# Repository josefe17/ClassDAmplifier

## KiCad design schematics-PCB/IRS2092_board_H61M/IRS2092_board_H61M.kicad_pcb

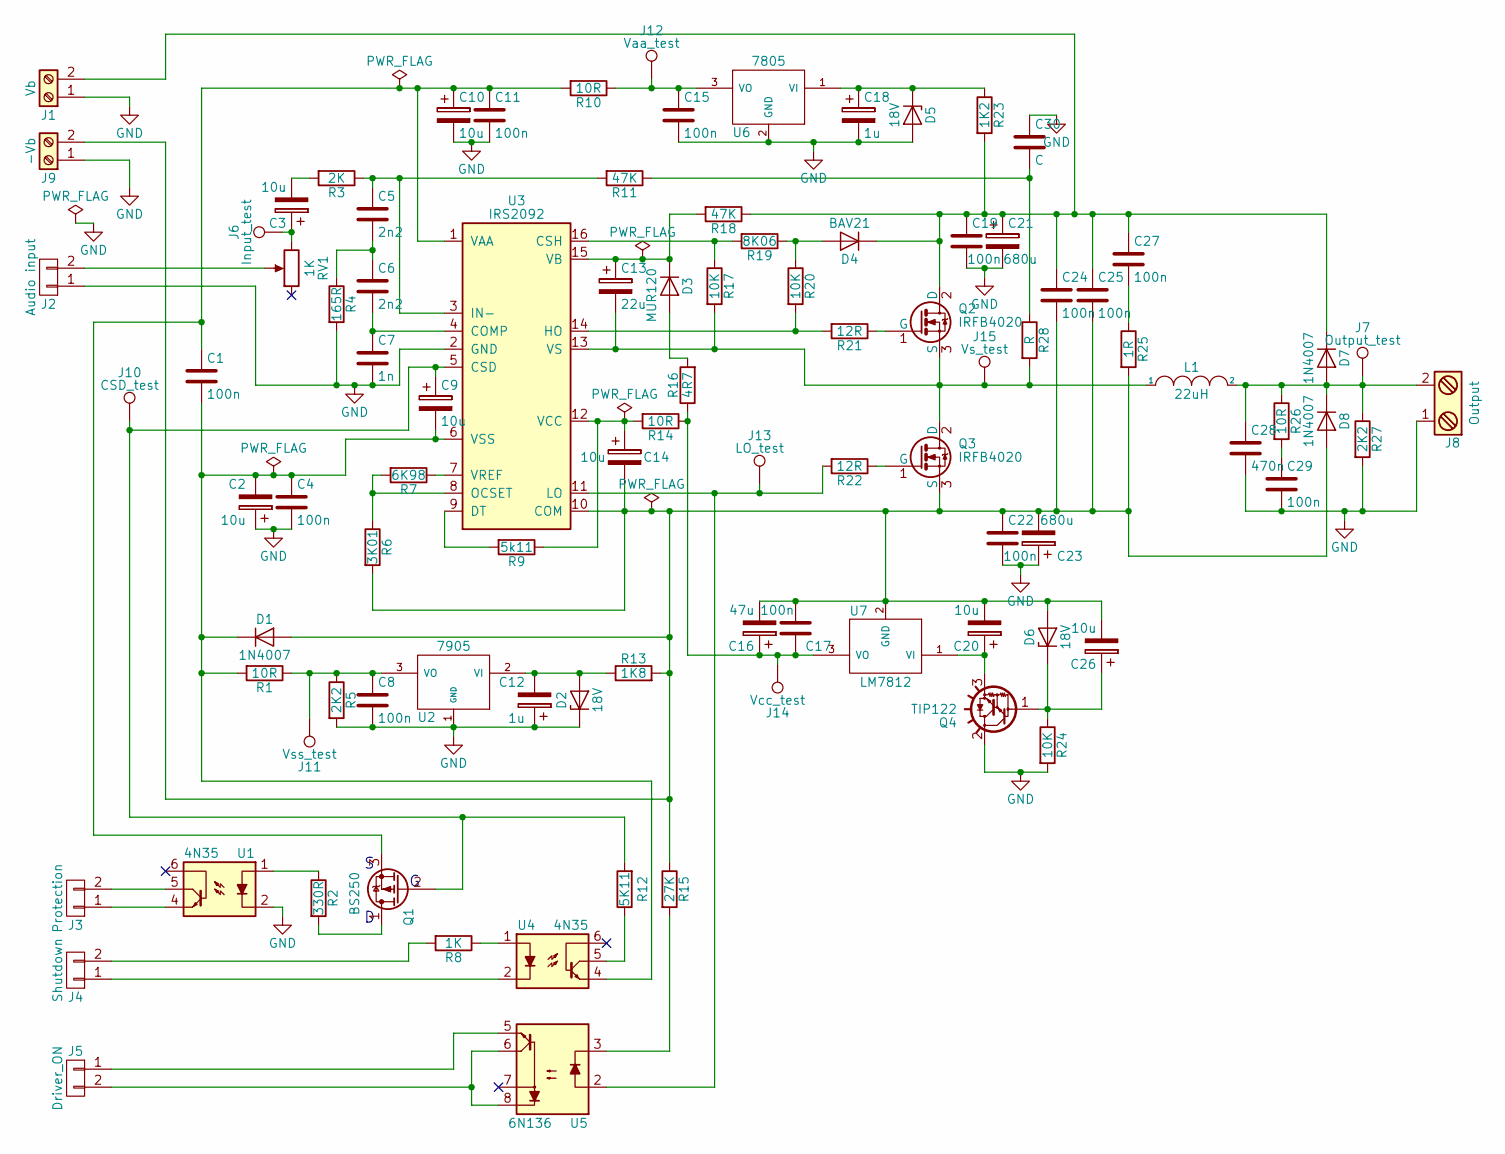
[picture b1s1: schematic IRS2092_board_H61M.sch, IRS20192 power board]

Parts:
C1, C4, C8, C11, C15, C17: 100n; C_Rect_L7.0mm_W2.5mm_P5.00mm
C2, C3, C9, C10, C14, C20, C26: 10u; CP_Radial_D8.0mm_P2.50mm
C5, C6: 2n2; C_Rect_L7.0mm_W2.5mm_P5.00mm
C7: 1n; C_Rect_L7.0mm_W2.5mm_P5.00mm
C12, C18: 1u; CP_Radial_D8.0mm_P2.50mm
C13: 22u; CP_Radial_D6.3mm_P2.50mm
C16: 47u; CP_Radial_D5.0mm_P2.00mm
C19, C22, C24, C25, C27, C29: 100n; C_Rect_L11.5mm_W4.0mm_P10.00mm_MKT
C21, C23: 680u; CP_Radial_D30.0mm_P10.00mm_SnapIn
C28: 470n; C_Rect_L16.5mm_W8.9mm_P15.00mm_MKT
C30: C; C_Rect_L7.0mm_W2.5mm_P5.00mm
D1, D7, D8: 1N4007; D_DO-41_SOD81_P10.16mm_Horizontal
D2, D5, D6: 18V; D_DO-41_SOD81_P10.16mm_Horizontal
D3: MUR120; D_DO-41_SOD81_P10.16mm_Horizontal
D4: BAV21; D_DO-35_SOD27_P10.16mm_Horizontal
J1: Vb; TerminalBlock_bornier-2_P5.08mm
J2: Audio input; Molex_KK-6410-02_02x2.54mm_Straight
J3: Protection; Molex_KK-6410-02_02x2.54mm_Straight
J4: Shutdown; Molex_KK-6410-02_02x2.54mm_Straight
J5: Driver_ON; Molex_KK-6410-02_02x2.54mm_Straight
J6: Input_test; PINTST
J7: Output_test; PINTST
J8: Output; TerminalBlock_bornier-2_P5.08mm
J9: -Vb; TerminalBlock_bornier-2_P5.08mm
J10: CSD_test; PINTST
J11: Vss_test; PINTST
J12: Vaa_test; PINTST
J13: LO_test; PINTST
J14: Vcc_test; PINTST
J15: Vs_test; PINTST
L1: 22uH; L_Toroid_Vertical_L41.9mm_W19.1mm_P15.80mm_Vishay_TJ7
Q1: BS250; TO-92_Inline_Narrow_Oval
Q2, Q3: IRFB4020; TO-220-3_Vertical
Q4: TIP122; TO-220-3_Vertical
R1, R10, R14: 10R; R_Axial_DIN0207_L6.3mm_D2.5mm_P10.16mm_Horizontal
R2: 330R; R_Axial_DIN0207_L6.3mm_D2.5mm_P10.16mm_Horizontal
R3: 2K; R_Axial_DIN0207_L6.3mm_D2.5mm_P10.16mm_Horizontal
R4: 165R; R_Axial_DIN0207_L6.3mm_D2.5mm_P10.16mm_Horizontal
R5: 2K2; R_Axial_DIN0207_L6.3mm_D2.5mm_P10.16mm_Horizontal
R6: 3K01; R_Axial_DIN0207_L6.3mm_D2.5mm_P10.16mm_Horizontal
R7: 6K98; R_Axial_DIN0207_L6.3mm_D2.5mm_P10.16mm_Horizontal
R8: 1K; R_Axial_DIN0207_L6.3mm_D2.5mm_P10.16mm_Horizontal
R9: 5k11; R_Axial_DIN0207_L6.3mm_D2.5mm_P10.16mm_Horizontal
R11, R18: 47K; R_Axial_DIN0207_L6.3mm_D2.5mm_P10.16mm_Horizontal
R12: 5K11; R_Axial_DIN0207_L6.3mm_D2.5mm_P10.16mm_Horizontal
R13: 1K8; R_Axial_DIN0516_L15.5mm_D5.0mm_P20.32mm_Horizontal
R15: 27K; R_Axial_DIN0207_L6.3mm_D2.5mm_P10.16mm_Horizontal
R16: 4R7; R_Axial_DIN0207_L6.3mm_D2.5mm_P10.16mm_Horizontal
R17, R20, R24: 10K; R_Axial_DIN0207_L6.3mm_D2.5mm_P10.16mm_Horizontal
R19: 8K06; R_Axial_DIN0207_L6.3mm_D2.5mm_P10.16mm_Horizontal
R21, R22: 12R; R_Axial_DIN0207_L6.3mm_D2.5mm_P10.16mm_Horizontal
R23: 1K2; R_Axial_DIN0516_L15.5mm_D5.0mm_P20.32mm_Horizontal
R25: 1R; R_Axial_DIN0516_L15.5mm_D5.0mm_P20.32mm_Horizontal
R26: 10R; R_Axial_DIN0516_L15.5mm_D5.0mm_P20.32mm_Horizontal
R27: 2K2; R_Axial_DIN0516_L15.5mm_D5.0mm_P20.32mm_Horizontal
R28: R; R_Axial_DIN0207_L6.3mm_D2.5mm_P10.16mm_Horizontal
RV1: 1K; Potentiometer_Trimmer_Vishay_T73XX_Vertical
U1, U4: 4N35; DIP-6_W7.62mm
U2: 7905; TO-220-3_Vertical
U3: IRS2092; SOIC-16_3.9x9.9mm_Pitch1.27mm
U5: 6N136; DIP-8_W7.62mm
U6: 7805; TO-220-3_Vertical
U7: LM7812; TO-220-3_Vertical

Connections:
GND: C2.1, C4.2, C7.2, C8.2, C10.2, C11.2, C12.1, C15.2, C18.2, C19.2, C21.2, C22.2, C23.1, C28.2, C29.2, C30.1, D2.1 (K), D5.2 (A), J1.1, J2.1, J8.1, J9.1, Q4.2 (C), R4.2, R5.2, R24.2, R27.2, U1.2, U2.1 (GND), U3.2 (GND), U6.2 (GND)
unnamed: C1.1, C10.1, C11.1, Q1.3 (S), R10.2, U3.1 (VAA)
unnamed: C1.2, C2.2, C4.1, C9.2, D1.1 (K), R1.2, U3.6 (VSS), U4.4
unnamed: C3.1, J6.1, RV1.3
unnamed: C3.2, R3.2
unnamed: C5.1, R3.1, R11.2, U3.3 (IN-)
unnamed: C5.2, C6.1, R4.1
unnamed: C6.2, C7.1, U3.4 (COMP)
unnamed: C8.1, J11.1, R1.1, R5.1, U2.3 (VO)
unnamed: C9.1, J10.1, Q1.2 (G), R12.2, U3.5 (CSD)
unnamed: C12.2, D2.2 (A), R13.1, U2.2 (VI)
unnamed: C13.1, D3.1 (K), R18.2, U3.15 (VB)
unnamed: C13.2, J15.1, L1.1, Q2.3 (S), Q3.2 (D), R17.2, R28.2, U3.13 (VS)
unnamed: C14.1, R9.1, R14.2, U3.12 (VCC)
unnamed: C14.2, C16.2, C17.1, C20.2, C22.1, C23.2, C24.2, C25.2, C26.2, D1.2 (A), D6.2 (A), D8.2 (A), J9.2, Q3.3 (S), R6.2, R13.2, R15.1, R25.2, U3.10 (COM), U7.2 (GND)
unnamed: C15.1, J12.1, R10.1, U6.3 (VO)
unnamed: C16.1, C17.2, J14.1, R14.1, R16.1, U7.3 (VO)
unnamed: C18.1, D5.1 (K), R23.1, U6.1 (VI)
unnamed: C19.1, C21.1, C24.1, C25.1, C27.1, D4.1 (K), D7.1 (K), J1.2, Q2.2 (D), R18.1, R23.2
unnamed: C20.1, Q4.3 (E), U7.1 (VI)
unnamed: C26.1, D6.1 (K), Q4.1 (B), R24.1
unnamed: C27.2, R25.1
unnamed: C28.1, D7.2 (A), D8.1 (K), J7.1, J8.2, L1.2, R26.1, R27.1
unnamed: C29.1, R26.2
unnamed: C30.2, R11.1, R28.1
unnamed: D3.2 (A), R16.2
unnamed: D4.2 (A), R19.1, R20.1
unnamed: J2.2, RV1.2
unnamed: J3.1, U1.4
unnamed: J3.2, U1.5
unnamed: J4.1, U4.2
unnamed: J4.2, R8.2
unnamed: J5.1, U5.5
unnamed: J5.2, U5.6, U5.8
unnamed: J13.1, R22.2, U3.11 (LO), U5.2
unnamed: Q1.1 (D), R2.2
unnamed: Q2.1 (G), R21.1
unnamed: Q3.1 (G), R22.1
unnamed: R2.1, U1.1
unnamed: R6.1, R7.2, U3.8 (OCSET)
unnamed: R7.1, U3.7 (VREF)
unnamed: R8.1, U4.1
unnamed: R9.2, U3.9 (DT)
unnamed: R12.1, U4.5
unnamed: R15.2, U5.3
unnamed: R17.1, R19.2, U3.16 (CSH)
unnamed: R20.2, R21.2, U3.14 (HO)

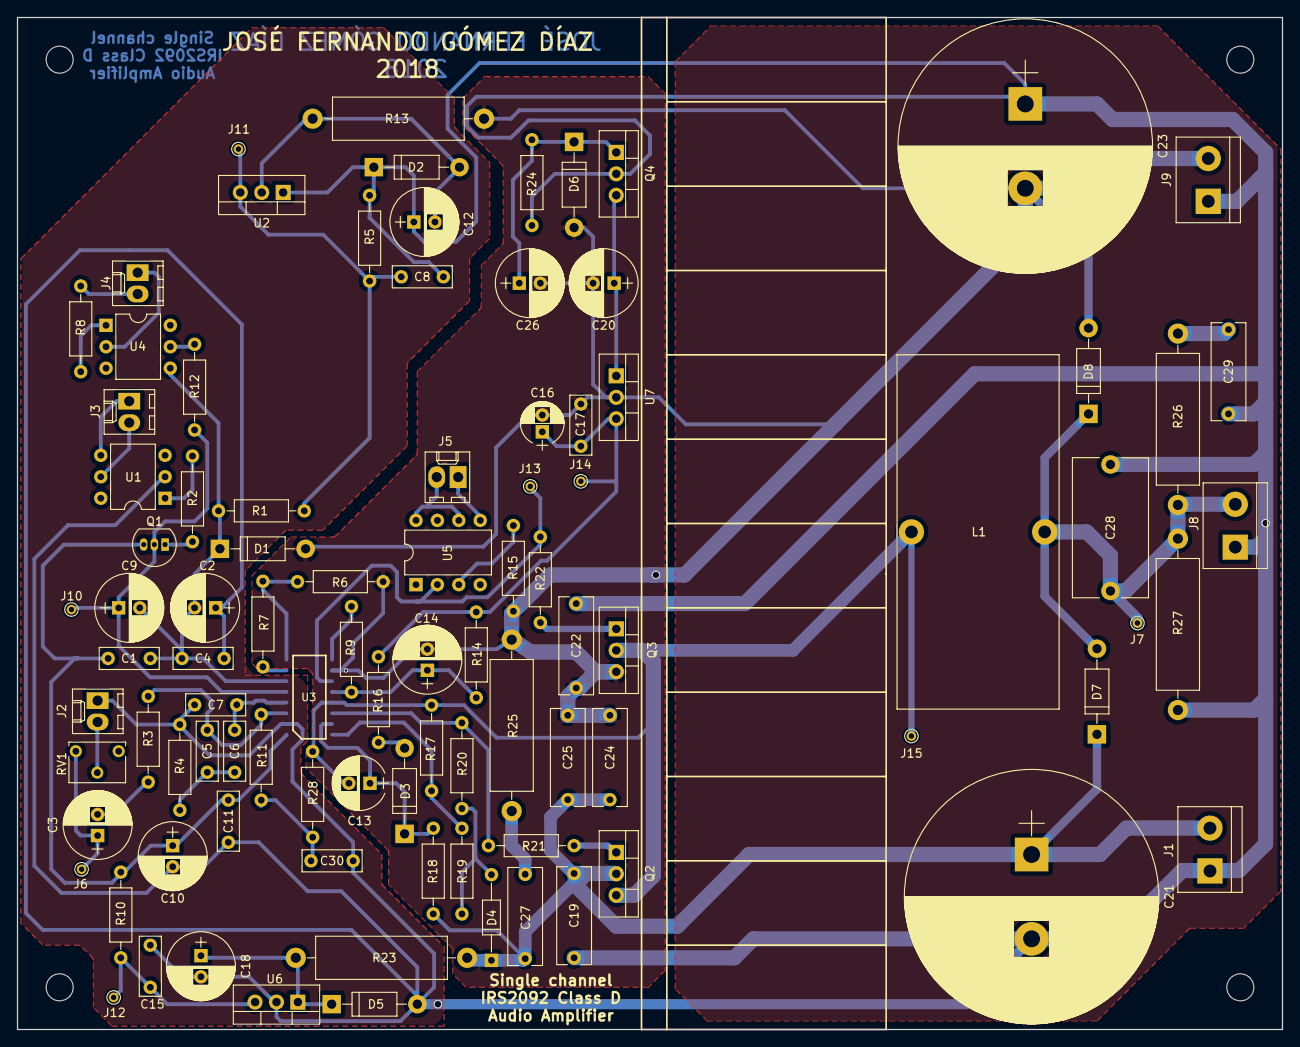
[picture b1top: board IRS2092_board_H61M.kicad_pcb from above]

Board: 2 copper layers, 150.0 x 120.0 mm, 96 parts (1 on the bottom side), 47 nets.

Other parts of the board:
 : MountingHole_3.2mm_M3
 #2: MountingHole_3.2mm_M3

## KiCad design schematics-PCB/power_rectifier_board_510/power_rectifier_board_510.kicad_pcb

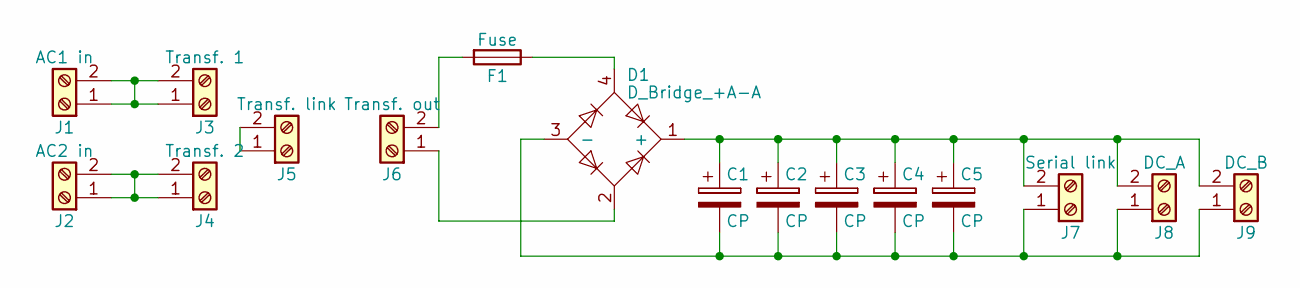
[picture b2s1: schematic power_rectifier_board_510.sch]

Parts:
C1, C2, C3: CP; CP_Radial_D30.0mm_P10.00mm_SnapIn
C4: CP; CP_Radial_D22.0mm_P10.00mm_SnapIn
C5: CP; CP_Radial_D18.0mm_P7.50mm
D1: D_Bridge_+A-A; bridge_kbpc_3506
F1: Fuse; Fuseholder5x20_horiz_open_universal_RSP
J1: AC1 in; TerminalBlock_bornier-2_P5.08mm
J2: AC2 in; TerminalBlock_bornier-2_P5.08mm
J3: Transf. 1; TerminalBlock_bornier-2_P5.08mm
J4: Transf. 2; TerminalBlock_bornier-2_P5.08mm
J5: Transf. link; TerminalBlock_bornier-2_P5.08mm
J6: Transf. out; TerminalBlock_bornier-2_P5.08mm
J7: Serial link; TerminalBlock_bornier-2_P5.08mm
J8: DC_A; TerminalBlock_bornier-2_P5.08mm
J9: DC_B; TerminalBlock_bornier-2_P5.08mm

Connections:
unnamed: C1.1, C2.1, C3.1, C4.1, C5.1, D1.1 (+), J7.2, J8.2, J9.2
unnamed: C1.2, C2.2, C3.2, C4.2, C5.2, D1.3 (-), J7.1, J8.1, J9.1
unnamed: D1.2, J6.1
unnamed: D1.4, F1.1
unnamed: F1.2, J6.2
unnamed: J1.1, J1.2, J3.1, J3.2
unnamed: J2.1, J2.2, J4.1, J4.2
unnamed: J5.1, J5.2

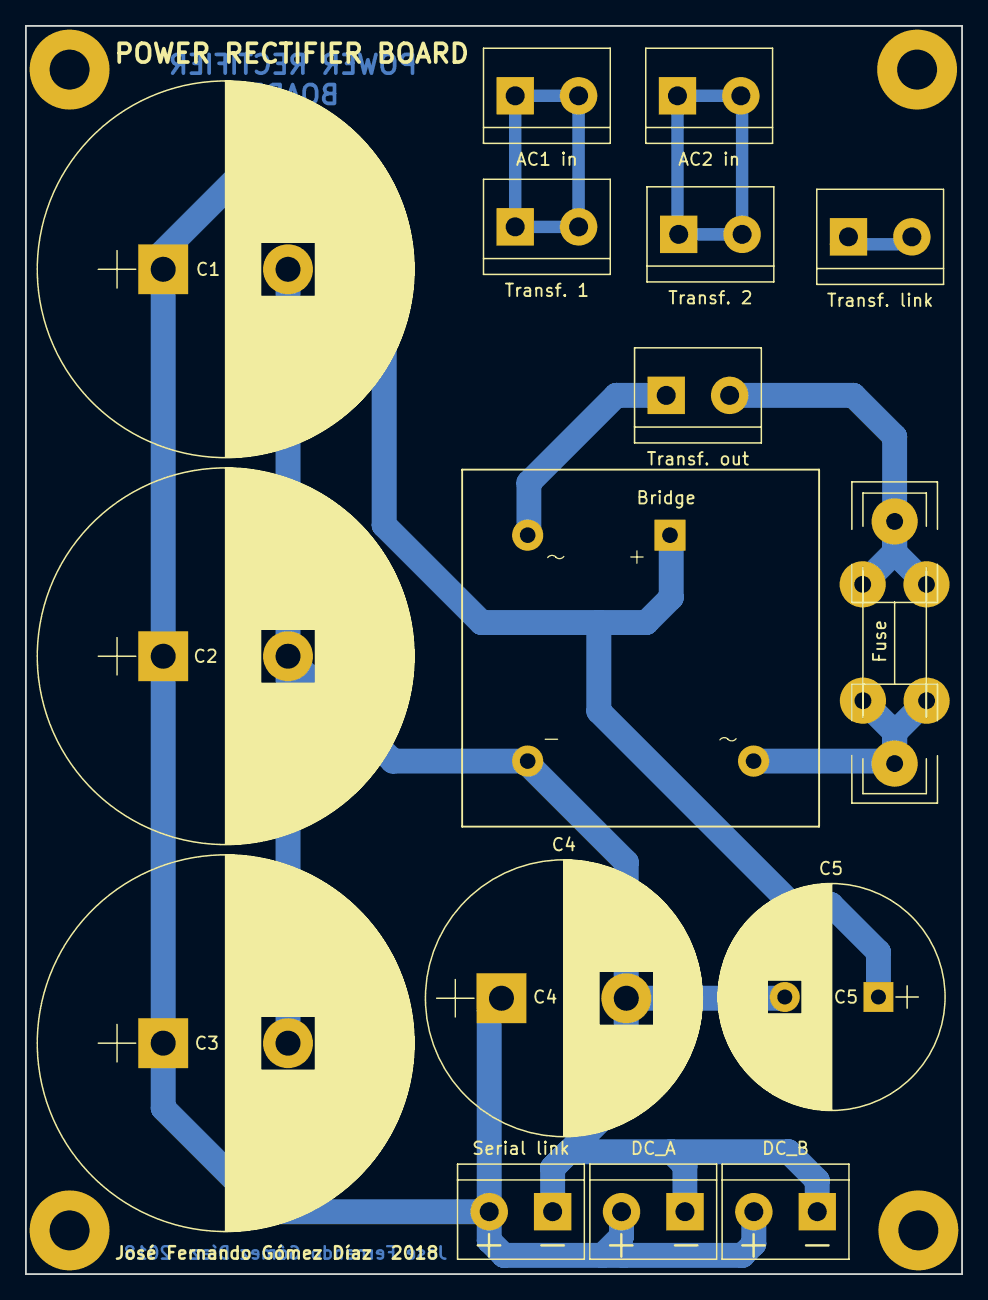
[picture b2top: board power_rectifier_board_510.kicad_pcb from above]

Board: 2 copper layers, 75.0 x 100.0 mm, 17 parts (0 on the bottom side), 8 nets.

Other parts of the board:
 Ref**: MountingHole_3.2mm_M3_Pad

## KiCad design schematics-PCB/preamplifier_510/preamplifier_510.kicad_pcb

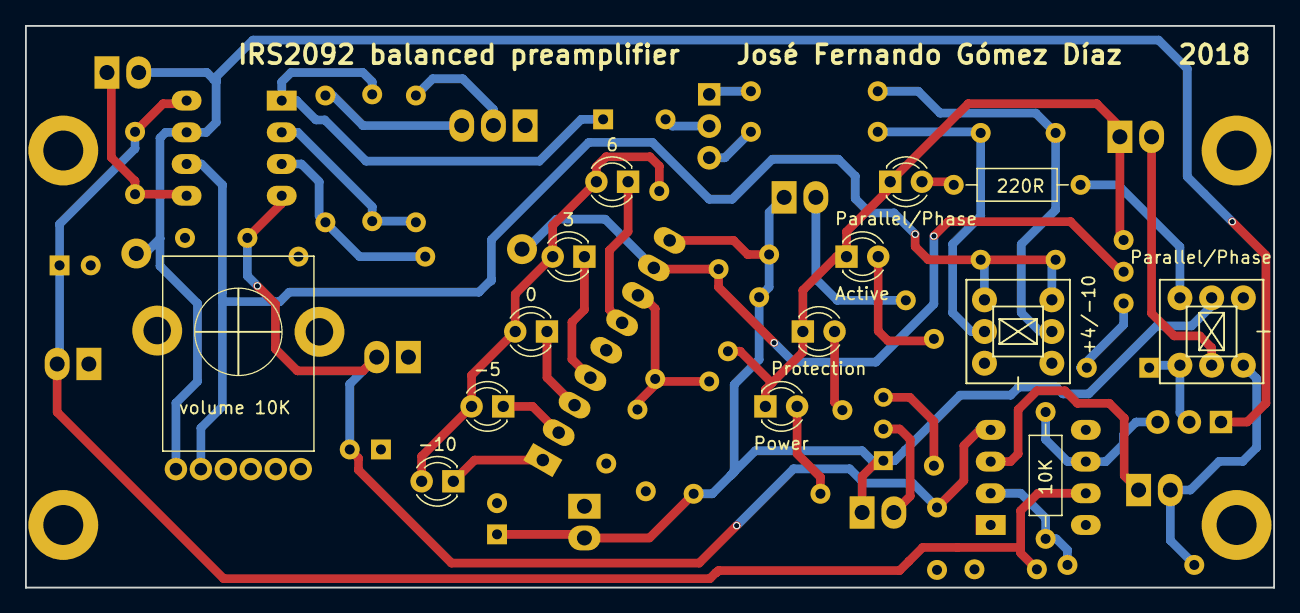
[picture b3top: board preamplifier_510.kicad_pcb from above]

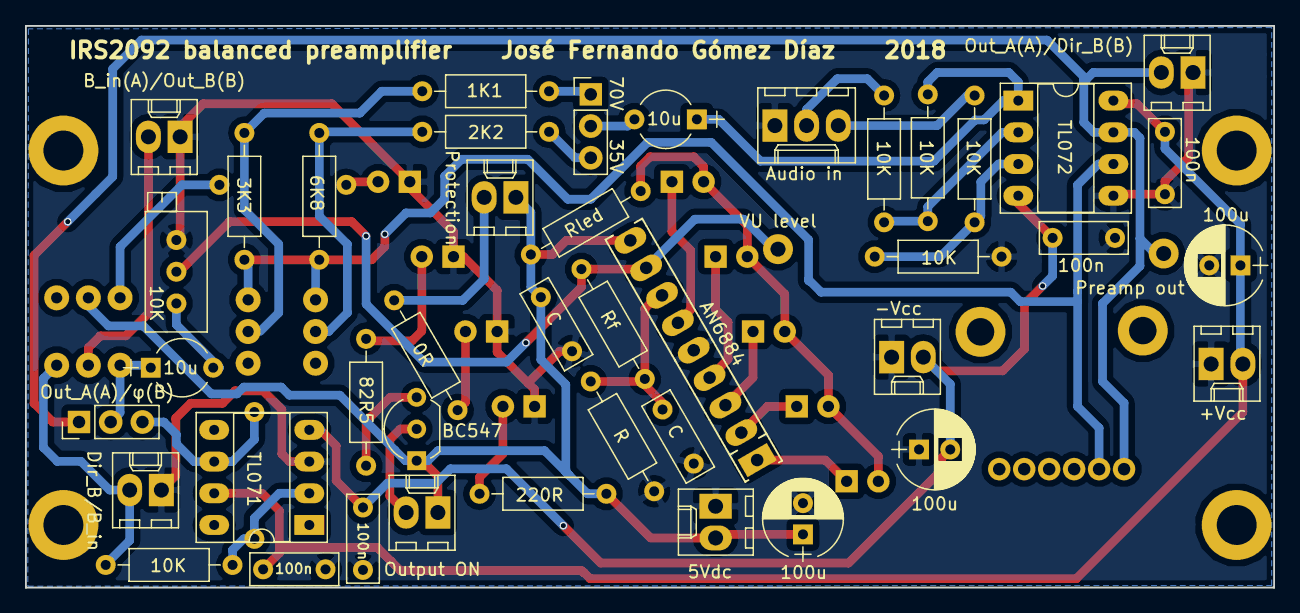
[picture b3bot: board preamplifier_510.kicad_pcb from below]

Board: 2 copper layers, 100.0 x 45.0 mm, 58 parts (44 on the bottom side), 38 nets.

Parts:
C1, C8, C9: 100u; CP_Radial_D6.3mm_P2.50mm
C3, C6: 10u; CP_Radial_Tantal_D4.5mm_P5.00mm
C4, C7: C; C_Rect_L7.0mm_W2.5mm_P5.00mm
C10, C11, C12, C13: 100n; C_Rect_L7.0mm_W2.5mm_P5.00mm
D1: Power; LED_D3.0mm
D2: Parallel/Phase; LED_D3.0mm
D3: Active; LED_D3.0mm
D4: Protection; LED_D3.0mm
D5: -10; LED_D3.0mm
D6: -5; LED_D3.0mm
D7: 0; LED_D3.0mm
D8: 3; LED_D3.0mm
D9: 6; LED_D3.0mm
J1: 5Vdc; Molex_KK-6410-02_02x2.54mm_Straight
J2: Audio in; Molex_KK-6410-03_03x2.54mm_Straight
J4: Output ON; Molex_KK-6410-02_02x2.54mm_Straight
J5: Protection; Molex_KK-6410-02_02x2.54mm_Straight
J6: -Vcc; Molex_KK-6410-02_02x2.54mm_Straight
J7: +Vcc; Molex_KK-6410-02_02x2.54mm_Straight
J8: Out_A(A)/Dir_B(B); Molex_KK-6410-02_02x2.54mm_Straight
J9: Dir_B/B_in; Molex_KK-6410-02_02x2.54mm_Straight
J10: B_in(A)/Out_B(B); Molex_KK-6410-02_02x2.54mm_Straight
J11: VU level; PINTST
J12: Preamp out; PINTST
JP1: 70V 35V; Pin_Header_Straight_1x03_Pitch2.54mm
JP2: Out_A(A)/φ(B); Pin_Header_Straight_1x03_Pitch2.54mm
Q1: BC547; TO-92_Inline_Wide
R1, R2: 220R; R_Axial_DIN0207_L6.3mm_D2.5mm_P10.16mm_Horizontal
R3, R4, R6, R7, R15, R16: 10K; R_Axial_DIN0207_L6.3mm_D2.5mm_P10.16mm_Horizontal
R5: 82R5; R_Axial_DIN0207_L6.3mm_D2.5mm_P10.16mm_Horizontal
R8: 0R; R_Axial_DIN0207_L6.3mm_D2.5mm_P10.16mm_Horizontal
R9: 1K1; R_Axial_DIN0207_L6.3mm_D2.5mm_P10.16mm_Horizontal
R10: 2K2; R_Axial_DIN0207_L6.3mm_D2.5mm_P10.16mm_Horizontal
R11: R; R_Axial_DIN0207_L6.3mm_D2.5mm_P10.16mm_Horizontal
R12: 3K3; R_Axial_DIN0207_L6.3mm_D2.5mm_P10.16mm_Horizontal
R13: 6K8; R_Axial_DIN0207_L6.3mm_D2.5mm_P10.16mm_Horizontal
R14: Rled; R_Axial_DIN0207_L6.3mm_D2.5mm_P10.16mm_Horizontal
R17: Rf; R_Axial_DIN0207_L6.3mm_D2.5mm_P10.16mm_Horizontal
RV1: volume 10K; Potentiometer_Alps_RK12L_Horizontal
RV2: 10K; Potentiometer_Trimmer_Bourns_3296X
SW1: Parallel/Phase; DPDT_Pushbutton
SW2: +4/-10; DPDT_Pushbutton
U1: TL072; DIP-8_W7.62mm_Socket_LongPads
U2: AN6884; SIP9_Housing_BigPads
U3: TL071; DIP-8_W7.62mm_Socket_LongPads

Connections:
GND: C1.2, C4.2, C7.2, C8.1, C9.2, C10.1, C11.2, C12.1, C13.2, D1.1, D2.1, D3.1, D4.1, J1.1, J2.1, J6.1, J7.1, J8.1, J9.1, J10.1, R6.2, R11.2, RV2.3, U1.5, U2.5, U3.3
unnamed: C1.1, C4.1, J1.2, J4.1, J5.1, Q1.1, R1.1, R14.2, SW1.2, U2.9
unnamed: C3.1, R7.1, U1.1
unnamed: C3.2, JP1.2
unnamed: C6.1, JP2.2, SW1.6
unnamed: C6.2, RV2.1
unnamed: C7.1, R11.1, R17.2, U2.7
unnamed: C8.2, C10.2, C12.2, J6.2, U1.4, U3.4
unnamed: C9.1, C11.1, C13.1, J7.2, U1.8, U3.7
unnamed: D1.2, R1.2
unnamed: D2.2, R2.2
unnamed: D3.2, R5.2
unnamed: D4.2, R8.2
unnamed: D5.1, U2.1
unnamed: D5.2, D6.2, D7.2, D8.2, D9.2, R14.1
unnamed: D6.1, U2.2
unnamed: D7.1, U2.3
unnamed: D8.1, U2.4
unnamed: D9.1, U2.6
unnamed: J2.2, R3.2
unnamed: J2.3, R4.2
unnamed: J4.2, Q1.2
unnamed: J5.2, R8.1
unnamed: J9.2, R15.2, SW1.4
unnamed: J10.2, SW1.5
unnamed: J11.1, R17.1, RV2.2, U2.8
unnamed: J8.2, J12.1, JP2.1, RV1.3, U1.7
unnamed: JP1.1, R9.2
unnamed: JP1.3, R10.2
unnamed: JP2.3, R16.1, U3.6
unnamed: Q1.3, R5.1
unnamed: R2.1, SW1.3
unnamed: R3.1, R7.2, U1.2
unnamed: R4.1, R6.1, U1.3
unnamed: R10.1, R13.2, SW2.5
unnamed: R12.1, R13.1, RV1.1, SW2.3, SW2.6, U1.6
unnamed: R9.1, R12.2, SW2.2
unnamed: R15.1, R16.2, U3.2

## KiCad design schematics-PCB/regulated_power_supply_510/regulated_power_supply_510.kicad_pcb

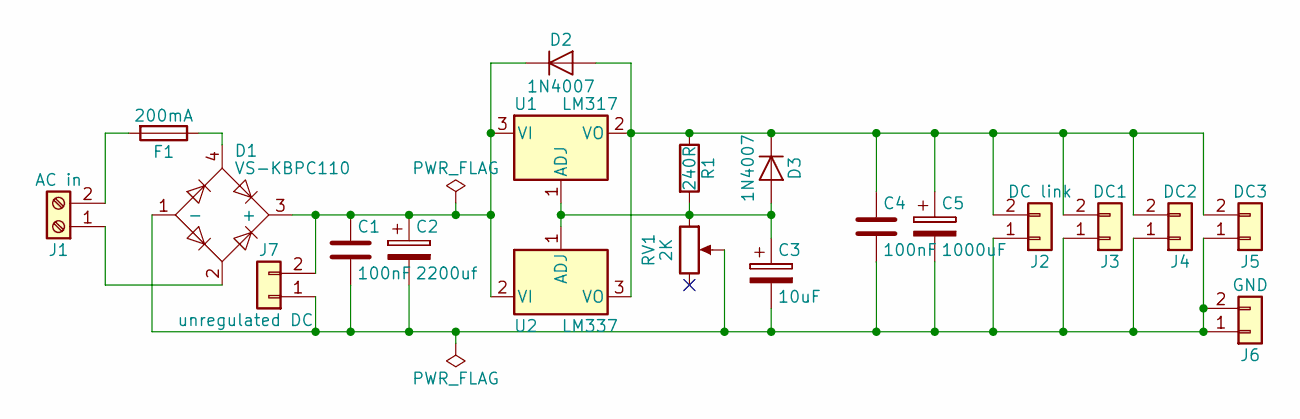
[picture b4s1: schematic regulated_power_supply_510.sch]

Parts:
C1, C4: 100nF; C_Rect_L7.0mm_W2.5mm_P5.00mm
C2: 2200uf; CP_Radial_D18.0mm_P7.50mm
C3: 10uF; CP_Radial_D8.0mm_P2.50mm
C5: 1000uF; CP_Radial_D18.0mm_P7.50mm
D1: VS-KBPC110; Diode_Bridge_15.7x15.7
D2, D3: 1N4007; D_DO-41_SOD81_P10.16mm_Horizontal
F1: 200mA; Fuseholder5x20_horiz_open_universal_RSP
J1: AC in; TerminalBlock_bornier-2_P5.08mm
J2: DC link; Molex_KK-6410-02_02x2.54mm_Straight
J3: DC1; Molex_KK-6410-02_02x2.54mm_Straight
J4: DC2; Molex_KK-6410-02_02x2.54mm_Straight
J5: DC3; Molex_KK-6410-02_02x2.54mm_Straight
J6: GND; Molex_KK-6410-02_02x2.54mm_Straight
J7: unregulated DC; Molex_KK-6410-02_02x2.54mm_Straight
R1: 240R; R_Axial_DIN0207_L6.3mm_D2.5mm_P10.16mm_Horizontal
RV1: 2K; Potentiometer_Trimmer_Vishay_T73XX_Vertical
U1: LM317; TO-220-3_Vertical
U2: LM337; TO-220-3_Vertical

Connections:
unnamed: C1.1, C2.1, D1.3 (+), D2.1 (K), J7.2, U1.3 (VI), U2.2 (VI)
unnamed: C1.2, C2.2, C3.2, C4.2, C5.2, D1.1 (-), J2.1, J3.1, J4.1, J5.1, J6.1, J6.2, J7.1, RV1.2
unnamed: C3.1, D3.2 (A), R1.2, RV1.1, U1.1 (ADJ), U2.1 (ADJ)
unnamed: C4.1, C5.1, D2.2 (A), D3.1 (K), J2.2, J3.2, J4.2, J5.2, R1.1, U1.2 (VO), U2.3 (VO)
unnamed: D1.2, J1.1
unnamed: D1.4, F1.1
unnamed: F1.2, J1.2

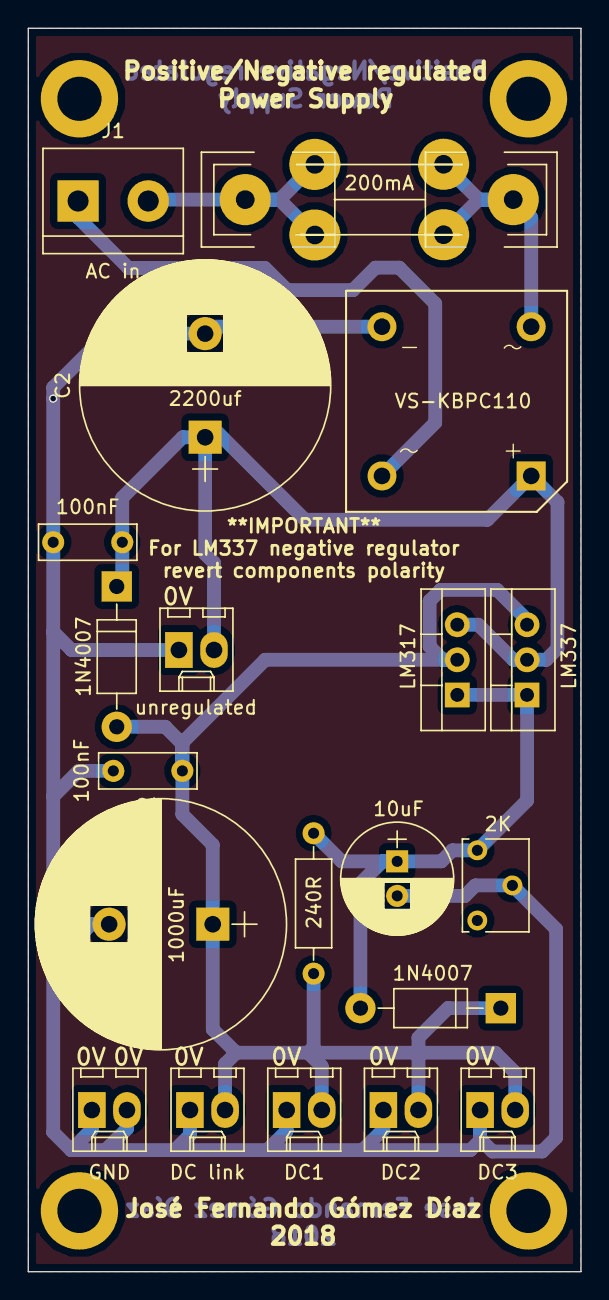
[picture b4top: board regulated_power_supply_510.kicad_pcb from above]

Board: 2 copper layers, 40.0 x 90.0 mm, 20 parts (0 on the bottom side), 7 nets.

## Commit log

2018-05-30 Initial released version
2018-05-30 Fixed previous commit errors
2018-05-30 Fixed more committing errors
2018-05-31 Updated block diagrams
